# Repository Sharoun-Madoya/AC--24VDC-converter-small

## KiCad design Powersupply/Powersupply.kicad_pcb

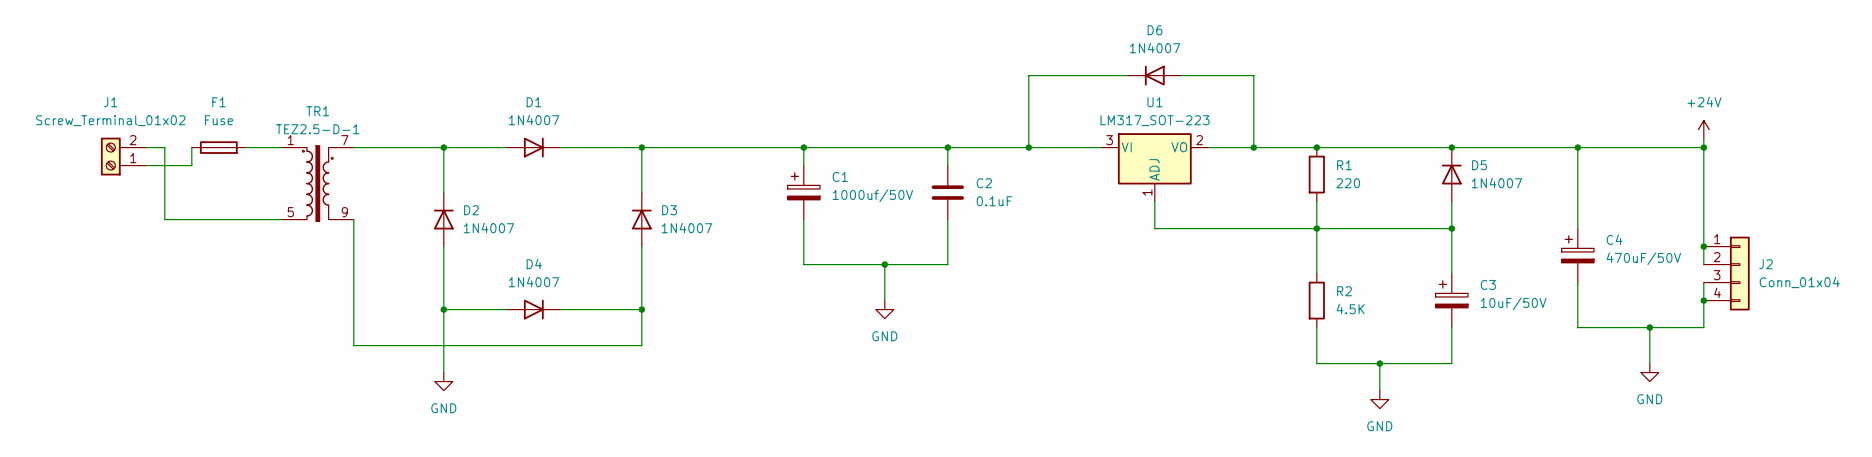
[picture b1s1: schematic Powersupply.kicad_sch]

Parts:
C1: 1000uf/50V; CP_Radial_D12.5mm_P7.50mm
C2: 0.1uF; C_0402_1005Metric
C3: 10uF/50V; CP_Radial_D12.5mm_P7.50mm
C4: 470uF/50V; CP_Radial_D12.5mm_P7.50mm
D1, D2, D3, D4, D5, D6: 1N4007; D_DO-41_SOD81_P10.16mm_Horizontal
F1: Fuse; Fuse_Bourns_MF-RHT550
J1: Screw_Terminal_01x02; TerminalBlock_Phoenix_MKDS-1,5-2_1x02_P5.00mm_Horizontal
J2: Conn_01x04; PhoenixContact_GMSTBA_2,5_4-G_1x04_P7.50mm_Horizontal
R1: 220; R_Axial_DIN0207_L6.3mm_D2.5mm_P10.16mm_Horizontal
R2: 4.5K; R_Axial_DIN0207_L6.3mm_D2.5mm_P10.16mm_Horizontal
TR1: TEZ2.5-D-1; Transformer_Breve_TEZ-28x33
U1: LM317_SOT-223; SOT-223-3_TabPin2

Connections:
+24V: C4.1, D5.1 (K), D6.2 (A), J2.1, J2.2, R1.1, U1.2 (VO)
GND: C1.2, C2.2, C3.2, C4.2, D2.2 (A), D4.2 (A), J2.3, J2.4, R2.2
unnamed: D1.2 (A), D2.1 (K), TR1.7
unnamed: C1.1, C2.1, D1.1 (K), D3.1 (K), D6.1 (K), U1.3 (VI)
unnamed: D3.2 (A), D4.1 (K), TR1.9
unnamed: C3.1, D5.2 (A), R1.2, R2.1, U1.1 (ADJ)
unnamed: F1.2, TR1.1
unnamed: F1.1, J1.1
unnamed: J1.2, TR1.5

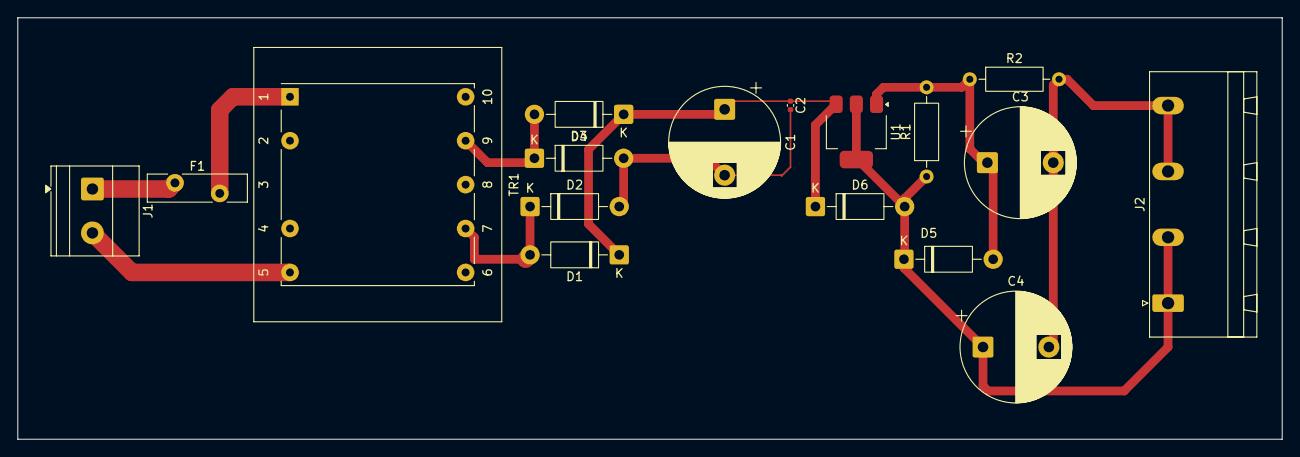
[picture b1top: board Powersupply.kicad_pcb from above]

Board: 2 copper layers, 144.0 x 48.0 mm, 17 parts (0 on the bottom side), 9 nets.

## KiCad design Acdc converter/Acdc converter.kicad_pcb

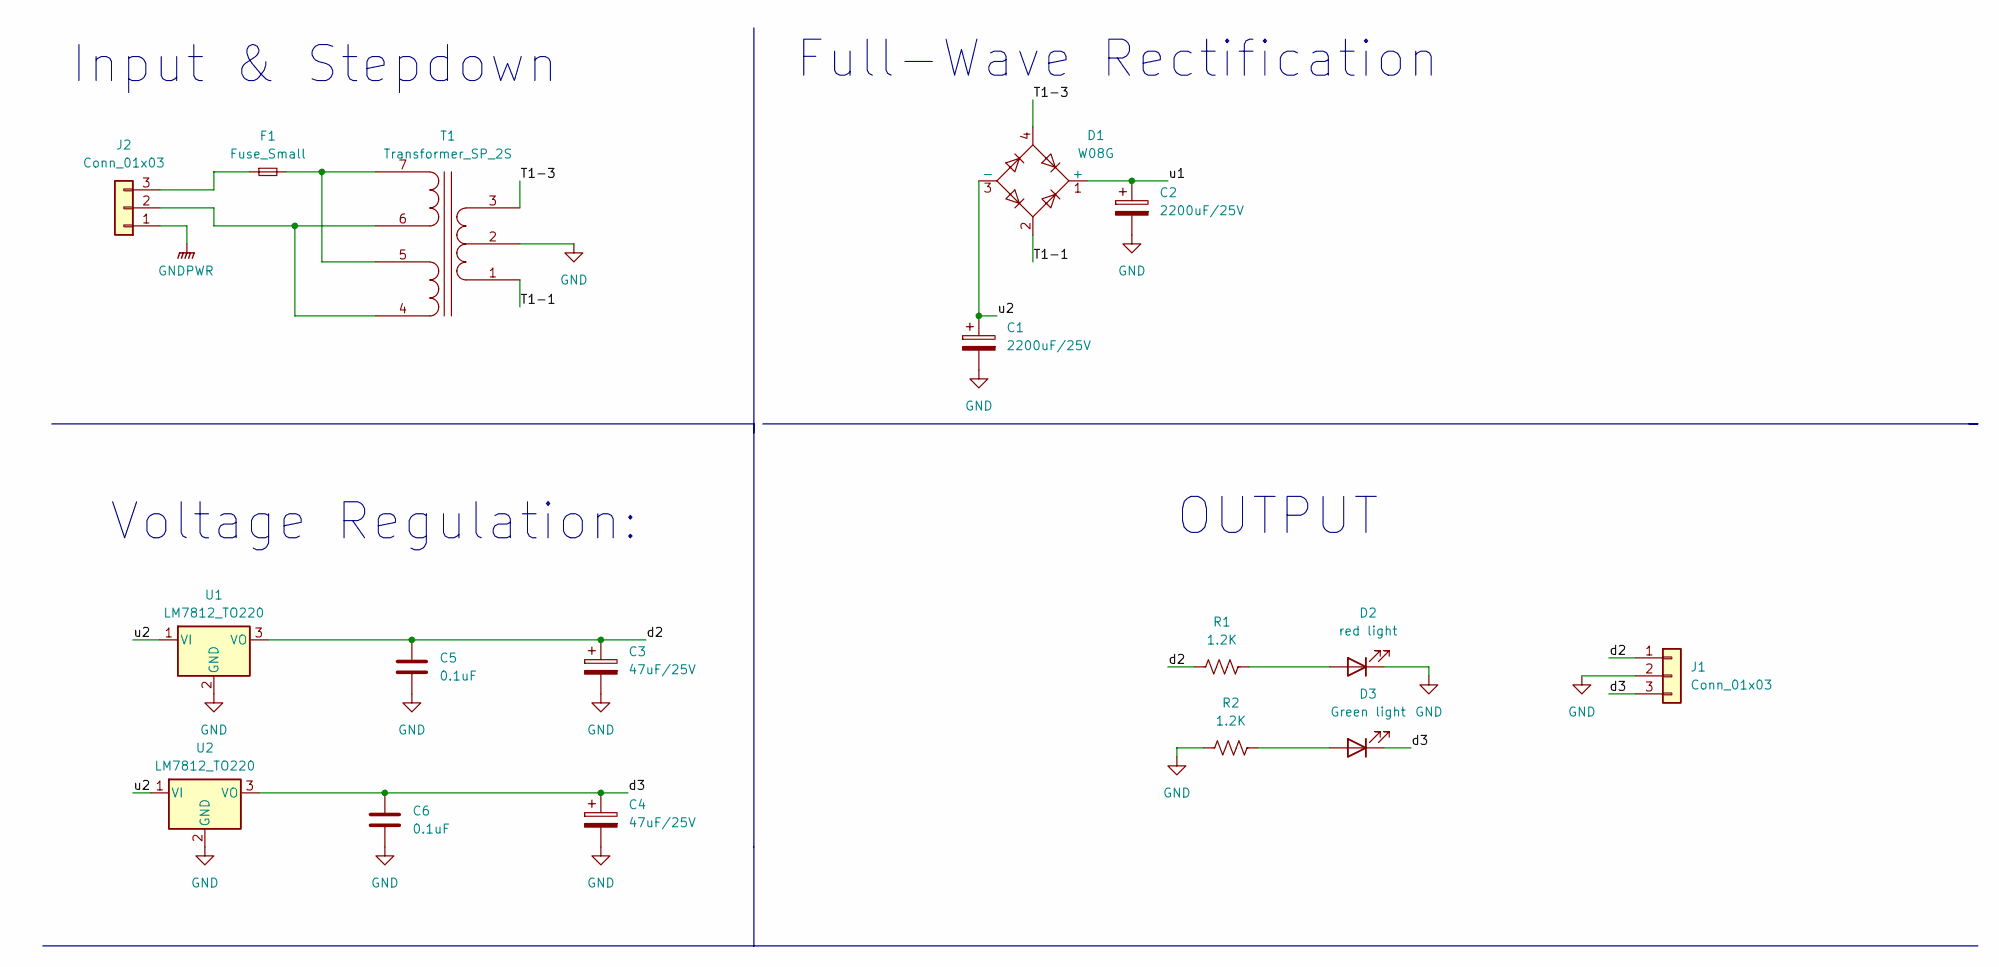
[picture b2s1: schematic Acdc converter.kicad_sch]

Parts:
C1, C2: 2200uF/25V; CP_Elec_10x14.3
C3, C4: 47uF/25V; CP_Elec_10x14.3
C5, C6: 0.1uF; CP_EIA-2012-15_AVX-P
D1: W08G; Diode_Bridge_Round_D9.8mm
D2: red light; LED_D3.0mm_Horizontal_O1.27mm_Z10.0mm
D3: Green light; LED_D3.0mm_Horizontal_O1.27mm_Z10.0mm
F1: Fuse_Small; Fuseholder_Cylinder-5x20mm_EATON_HBW_Vertical_Closed
J1, J2: Conn_01x03; PhoenixContact_GMSTBA_2,5_3-G-7,62_1x03_P7.62mm_Horizontal
R1, R2: 1.2K; R_0201_0603Metric_Pad0.64x0.40mm_HandSolder
T1: Transformer_SP_2S; Transformer_CHK_EI30-2VA_1xSec
U1, U2: LM7812_TO220; TO-220-3_Vertical

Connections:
/T1-1: D1.2, T1.1 (IN+)
/T1-3: D1.4, T1.3 (OUT2A)
/d2: C3.1, C5.1, J1.1 (Pin_3), R1.1, U1.3 (VO)
/d3: C4.1, C6.1, D3.1 (K), J1.3 (Pin_1), U2.3 (VO)
/u1: C2.1, D1.1 (+)
/u2: C1.1, D1.3 (-), U1.1 (VI), U2.1 (VI)
GND: C1.2, C2.2, C3.2, C4.2, C5.2, C6.2, D2.1 (K), J1.2, R2.1, T1.2 (PM), U1.2 (GND), U2.2 (GND)
GNDPWR: J2.1
unnamed: D2.2 (A), R1.2
unnamed: D3.2 (A), R2.2
unnamed: J2.2, T1.4 (IN+), T1.6 (IN-)
unnamed: F1.1, J2.3
unnamed: F1.2, T1.5 (OUT1B), T1.7 (PM)

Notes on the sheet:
Input & Stepdown
Voltage Regulation:
Full-Wave Rectification
OUTPUT

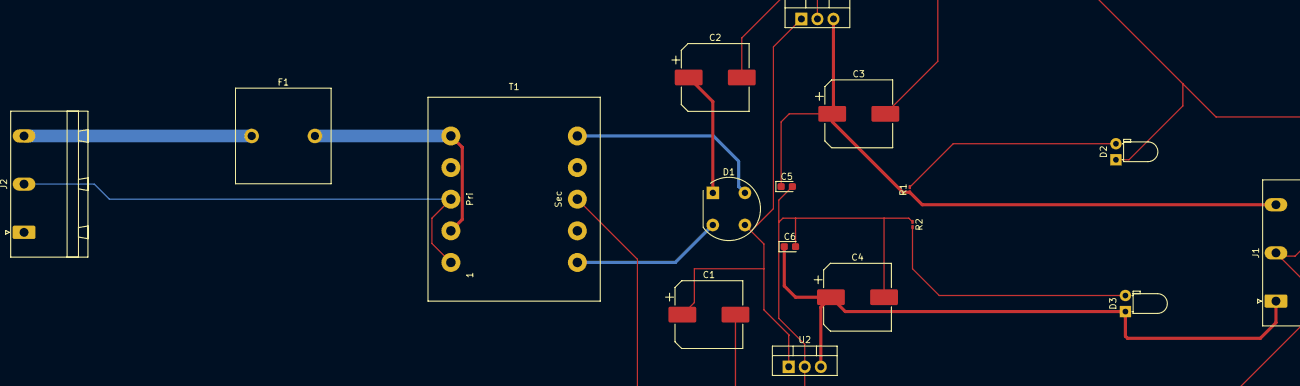
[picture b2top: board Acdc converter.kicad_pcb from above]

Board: 2 copper layers, 17 parts (0 on the bottom side), 12 nets.

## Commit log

2025-06-16 :tada:Started
2025-06-16 :sparkles: added stepdown transformer
2025-06-16 :memo : labelled circuit diagram
2025-06-17 :construction: placed components on editor
2025-06-21 ::rocket::completed retouching and connecting the components
2025-11-07 :tada:Finalizing
2025-11-07 :white_check_mark:Upadted a 240V power supply as an alternative
